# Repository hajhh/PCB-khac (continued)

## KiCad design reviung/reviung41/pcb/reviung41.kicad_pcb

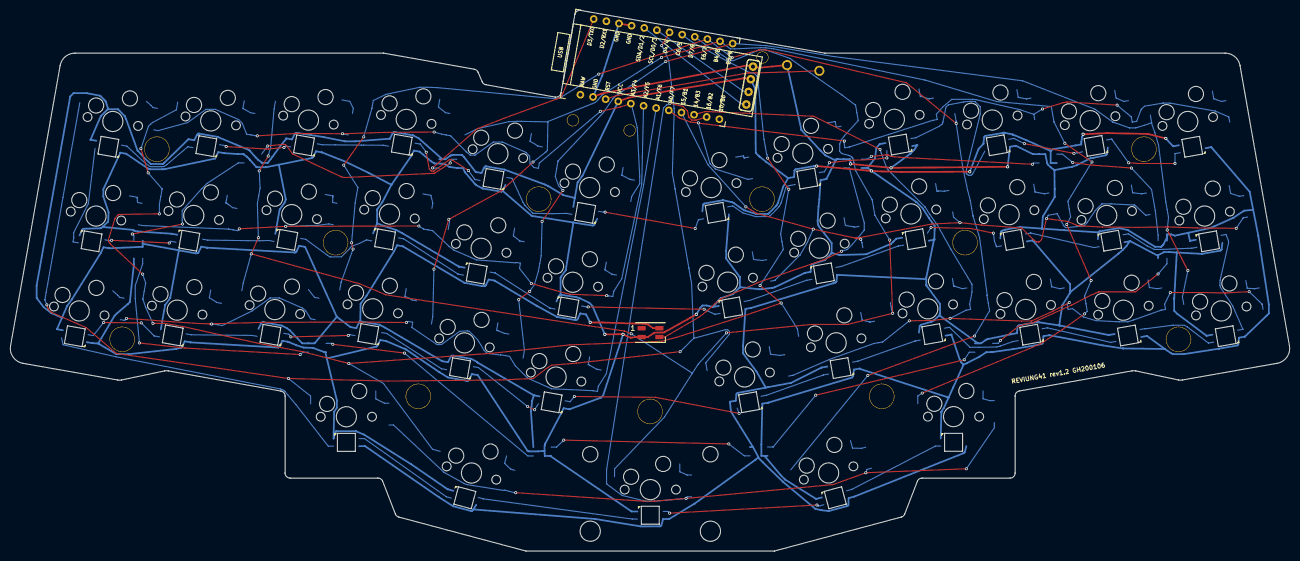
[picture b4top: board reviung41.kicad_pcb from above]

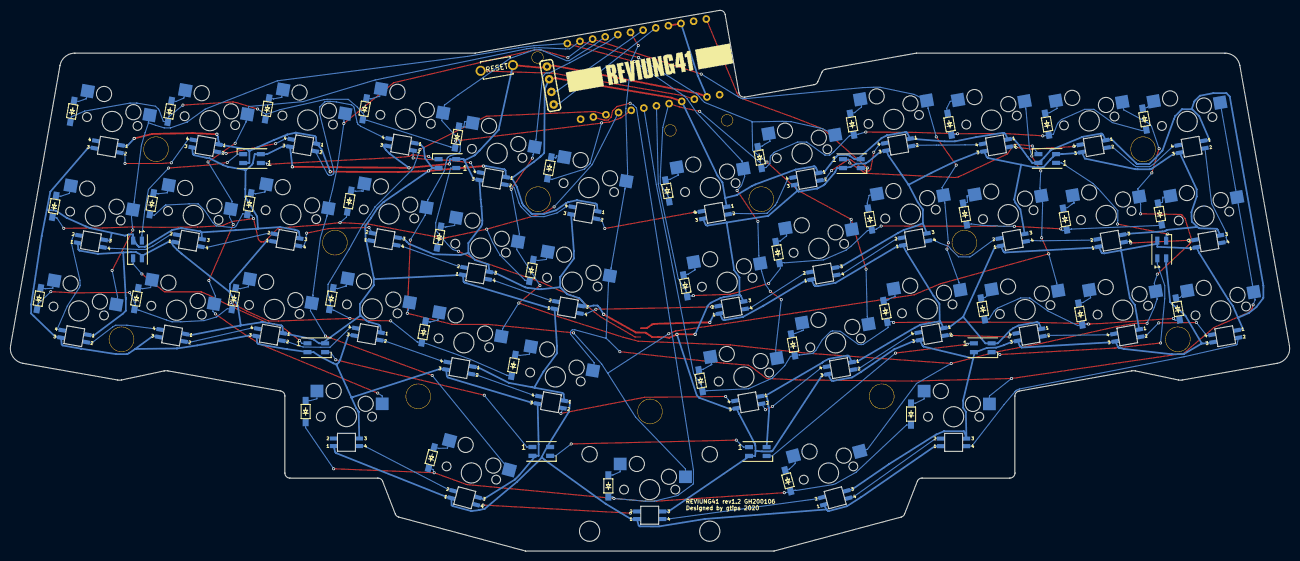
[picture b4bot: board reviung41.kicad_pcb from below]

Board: 2 copper layers, 253.3 x 107.1 mm, 153 parts (53 on the bottom side), 110 nets.

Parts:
D1, D2, D3, D4, D5, D6, D7, D8, D9, D10, D11, D12, D13, D14, D15, D16, D17, D18, D19, D20, D21, D22, D23, D24, D25, D26, D27, D28, D29, D30, D31, D32, D33, D34, D35, D36, D37, D38, D39, D40, D41: 1N4148W; Diode
D42, D43, D44, D45, D46, D47, D48, D49, D50, D51, D52: SK6812-mini
D53, D54, D55, D56, D57, D58, D59, D60, D61, D62, D63, D64, D75, D76, D77, D78, D79, D80, D81, D82, D83, D86, D87, D88: SK6812Mini-E
D65, D66, D67, D68, D69, D70, D71, D72, D73, D74, D84, D85, D89, D90, D91, D92, D93: SK6812-Mini-E-L2R
H1: Stab
H2, H7, H9, H10, H12, H13, H14, H15, H16, H17, H18: Hole
H3, H5, H8: Hole-M2
H4: LOGO
J1: OLED; OLED-0.91
RESET1: SW_PUSH; ResetSW_1side
SW1, SW2, SW3, SW4, SW5, SW6, SW7, SW8, SW9, SW10, SW11, SW12, SW13, SW14, SW15, SW16, SW17, SW18, SW19, SW20, SW21, SW22, SW23, SW24, SW25, SW26, SW27, SW28, SW29, SW30, SW31, SW32, SW33, SW34, SW35, SW36, SW37, SW38, SW40, SW41: SW_PUSH; SW-MX-hotswap
SW39: SW_2U_PUSH; SW-MX-hotswap
U1: ProMicro

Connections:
GND: D42.2, D43.2, D44.2, D45.2, D46.2, D47.2, D48.2, D49.2, D50.2, D51.2, D52.2, D53.2, D54.2, D55.2, D56.2, D57.2, D58.2, D59.2, D60.2, D61.2, D62.2, D63.2, D64.2, D65.2, D66.2, D67.2, D68.2, D69.2, D70.2, D71.2, D72.2, D73.2, D74.2, D75.2, D76.2, D77.2, D78.2, D79.2, D80.2, D81.2, D82.2, D83.2, D84.2, D85.2, D86.2, D87.2, D88.2, D89.2, D90.2, D91.2, D92.2, D93.2, J1.4, RESET1.2, U1.3, U1.4, U1.23
LED: D42.3, U1.1
unnamed: D1.2, SW1.2
unnamed: D2.2, SW2.2
unnamed: D3.2, SW3.2
unnamed: D4.2, SW4.2
unnamed: D5.2, SW5.2
unnamed: D6.2, SW6.2
unnamed: D7.2, SW7.2
unnamed: D8.2, SW8.2
unnamed: D9.2, SW9.2
unnamed: D10.2, SW10.2
unnamed: D11.2, SW11.2
unnamed: D12.2, SW12.2
unnamed: D13.2, SW13.2
unnamed: D14.2, SW14.2
unnamed: D15.2, SW15.2
unnamed: D16.2, SW16.2
unnamed: D17.2, SW17.2
unnamed: D18.2, SW18.2
unnamed: D19.2, SW19.2
unnamed: D20.2, SW20.2
unnamed: D21.2, SW21.2
unnamed: D22.2, SW22.2
unnamed: D23.2, SW23.2
unnamed: D24.2, SW24.2
unnamed: D25.2, SW25.2
unnamed: D26.2, SW26.2
unnamed: D27.2, SW27.2
unnamed: D28.2, SW28.2
unnamed: D29.2, SW29.2
unnamed: D30.2, SW30.2
unnamed: D31.2, SW31.2
unnamed: D32.2, SW32.2
unnamed: D33.2, SW33.2
unnamed: D34.2, SW34.2
unnamed: D35.2, SW35.2
unnamed: D36.2, SW36.2
unnamed: D37.2, SW37.2
unnamed: D38.2, SW38.2
unnamed: D39.2, SW39.2
unnamed: D40.2, SW40.2
unnamed: D41.2, SW41.2
unnamed: D42.1, D43.3
unnamed: D43.1, D44.3
unnamed: D44.1, D45.3
unnamed: D45.1, D46.3
unnamed: D46.1, D47.3
unnamed: D47.1, D48.3
unnamed: D48.1, D49.3
unnamed: D49.1, D50.3
unnamed: D50.1, D51.3
unnamed: D51.1, D52.3
unnamed: D53.1, D64.3
unnamed: D53.3, D54.1
unnamed: D54.3, D55.1
unnamed: D55.3, D56.1
unnamed: D56.3, D57.1
unnamed: D57.3, D58.1
unnamed: D58.3, D59.1
unnamed: D59.3, D60.1
unnamed: D60.3, D61.1
unnamed: D61.3, D62.1
unnamed: D62.3, D63.1
unnamed: D64.1, D65.3
unnamed: D65.1, D66.3
unnamed: D66.1, D67.3
unnamed: D67.1, D68.3
unnamed: D68.1, D69.3
unnamed: D69.1, D70.3
unnamed: D70.1, D71.3
unnamed: D71.1, D72.3
unnamed: D72.1, D73.3
unnamed: D73.1, D74.3
unnamed: D74.1, D85.3
unnamed: D75.1, D86.3
unnamed: D75.3, D76.1
unnamed: D76.3, D77.1
unnamed: D77.3, D78.1
unnamed: D78.3, D79.1
unnamed: D79.3, D80.1
unnamed: D80.3, D81.1
unnamed: D81.3, D82.1
unnamed: D82.3, D83.1
unnamed: D83.3, D84.1
unnamed: D84.3, D85.1
unnamed: D86.1, D87.3
unnamed: D87.1, D88.3
unnamed: D88.1, D89.3
unnamed: D89.1, D90.3
unnamed: D90.1, D91.3
unnamed: D91.1, D92.3
unnamed: D92.1, D93.3
SCL: J1.2, U1.6
SDA: J1.1, U1.5
VCC: D42.4, D43.4, D44.4, D45.4, D46.4, D47.4, D48.4, D49.4, D50.4, D51.4, D52.4, D53.4, D54.4, D55.4, D56.4, D57.4, D58.4, D59.4, D60.4, D61.4, D62.4, D63.4, D64.4, D65.4, D66.4, D67.4, D68.4, D69.4, D70.4, D71.4, D72.4, D73.4, D74.4, D75.4, D76.4, D77.4, D78.4, D79.4, D80.4, D81.4, D82.4, D83.4, D84.4, D85.4, D86.4, D87.4, D88.4, D89.4, D90.4, D91.4, D92.4, D93.4, J1.3, U1.21
col0: SW1.1, SW7.1, SW13.1, SW19.1, SW25.1, SW31.1, SW37.1, U1.7
col1: SW2.1, SW8.1, SW14.1, SW20.1, SW26.1, SW32.1, SW38.1, U1.8
col2: SW3.1, SW9.1, SW15.1, SW21.1, SW27.1, SW33.1, SW39.1, U1.9
col3: SW4.1, SW10.1, SW16.1, SW22.1, SW28.1, SW34.1, SW40.1, U1.10
col4: SW5.1, SW11.1, SW17.1, SW23.1, SW29.1, SW35.1, SW41.1, U1.11
col5: SW6.1, SW12.1, SW18.1, SW24.1, SW30.1, SW36.1, U1.12
reset: RESET1.1, U1.22
row0: D1.1, D2.1, D3.1, D4.1, D5.1, D6.1, U1.20
row1: D7.1, D8.1, D9.1, D10.1, D11.1, D12.1, U1.19
row2: D13.1, D14.1, D15.1, D16.1, D17.1, D18.1, U1.18
row3: D19.1, D20.1, D21.1, D22.1, D23.1, D24.1, U1.17
row4: D25.1, D26.1, D27.1, D28.1, D29.1, D30.1, U1.16
row5: D31.1, D32.1, D33.1, D34.1, D35.1, D36.1, U1.15
row6: D37.1, D38.1, D39.1, D40.1, D41.1, U1.14
